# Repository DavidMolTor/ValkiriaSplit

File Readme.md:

# VALKIRIA SPLIT

Completely wireless, split mechanical keyboard based on the nRF52840 microcontroller, with independent wireless operation for each half.

## Introduction

This is a personal project born from my interest in exploring the world of ergonomic mechanical keyboards. After looking at several existing designs, I found that none of them offered exactly what I was looking for, so I decided to design and build my own.

I took a bit of a gamble by choosing a Corne-inspired layout without a dedicated number row, opting for a more minimal design. However, if I find that this layout does not suit my needs, I plan to develop a new version with additional keys.

## Features

 - Completely wireless operation of both sides.

 - Rechargeable and replaceable battery.

 - Hot-swappable chocolate sockets.

 - Full RGB with switchable regulator.

 - Two 1.08" MIP displays.

 - Rotary encoders with push button.

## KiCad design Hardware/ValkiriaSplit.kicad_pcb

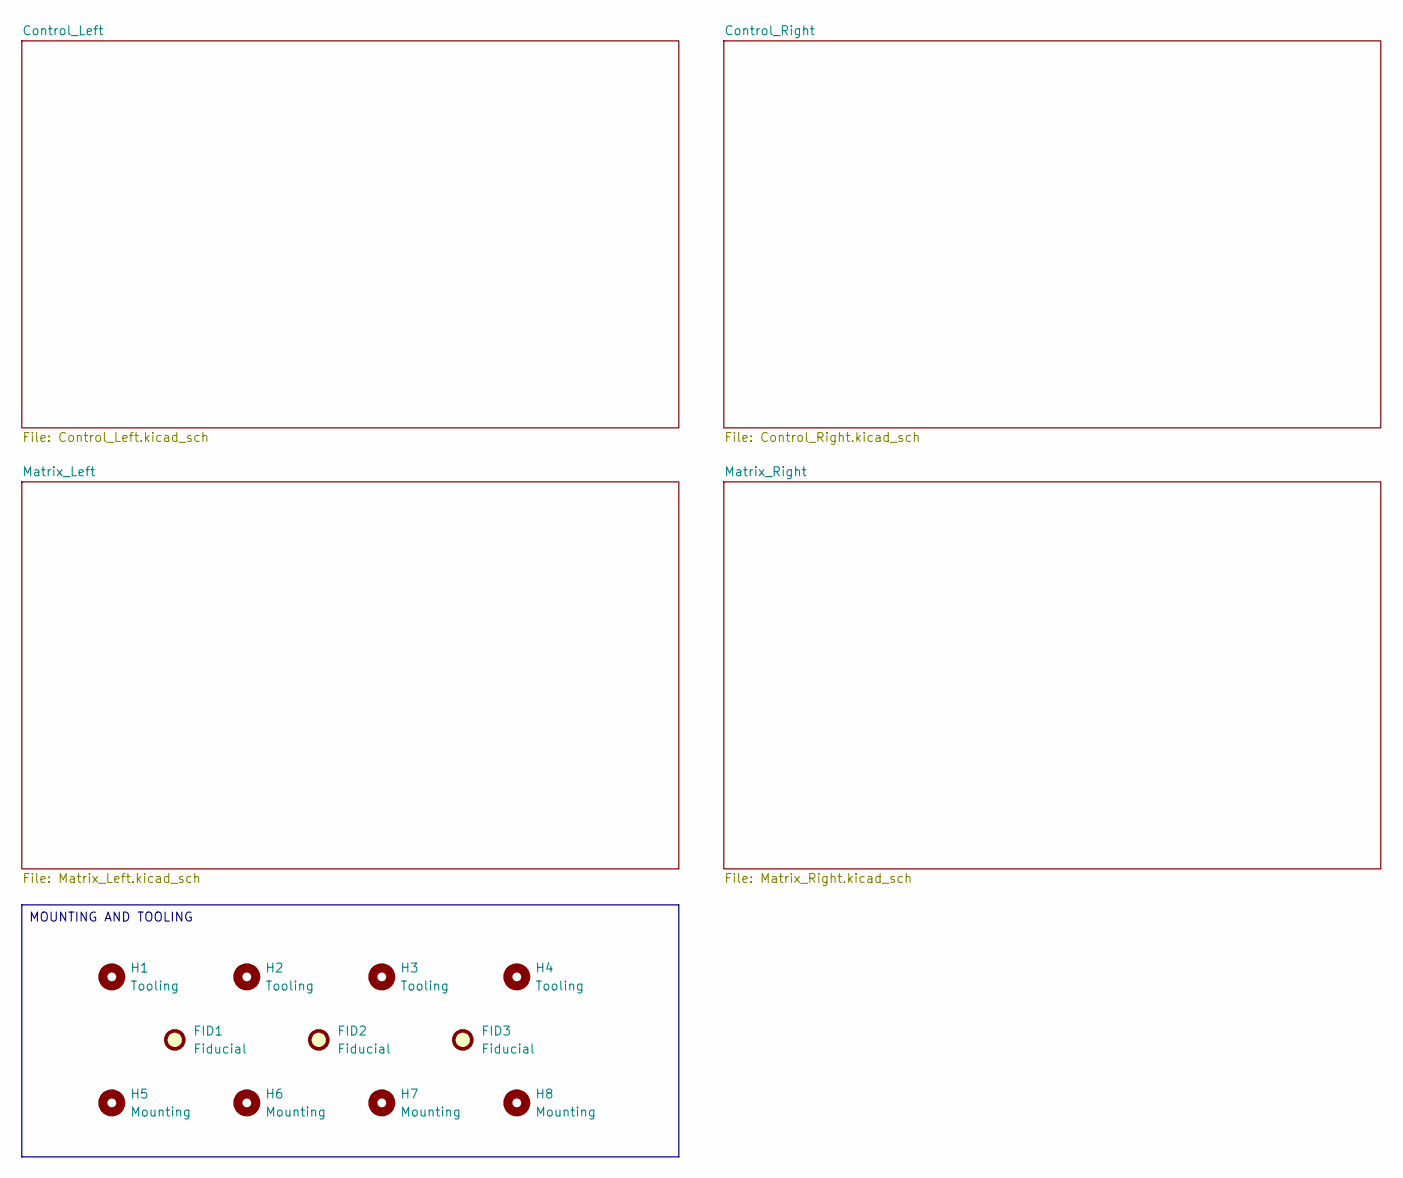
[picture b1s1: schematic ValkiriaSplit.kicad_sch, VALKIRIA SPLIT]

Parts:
FID1, FID2, FID3: Fiducial; Fiducial_1mm_Mask2mm
H1, H2, H3, H4: Tooling; ToolingHole_1.152mm
H5, H6, H7, H8: Mounting; MountingHole_2.2mm_M2

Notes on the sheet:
MOUNTING AND TOOLING

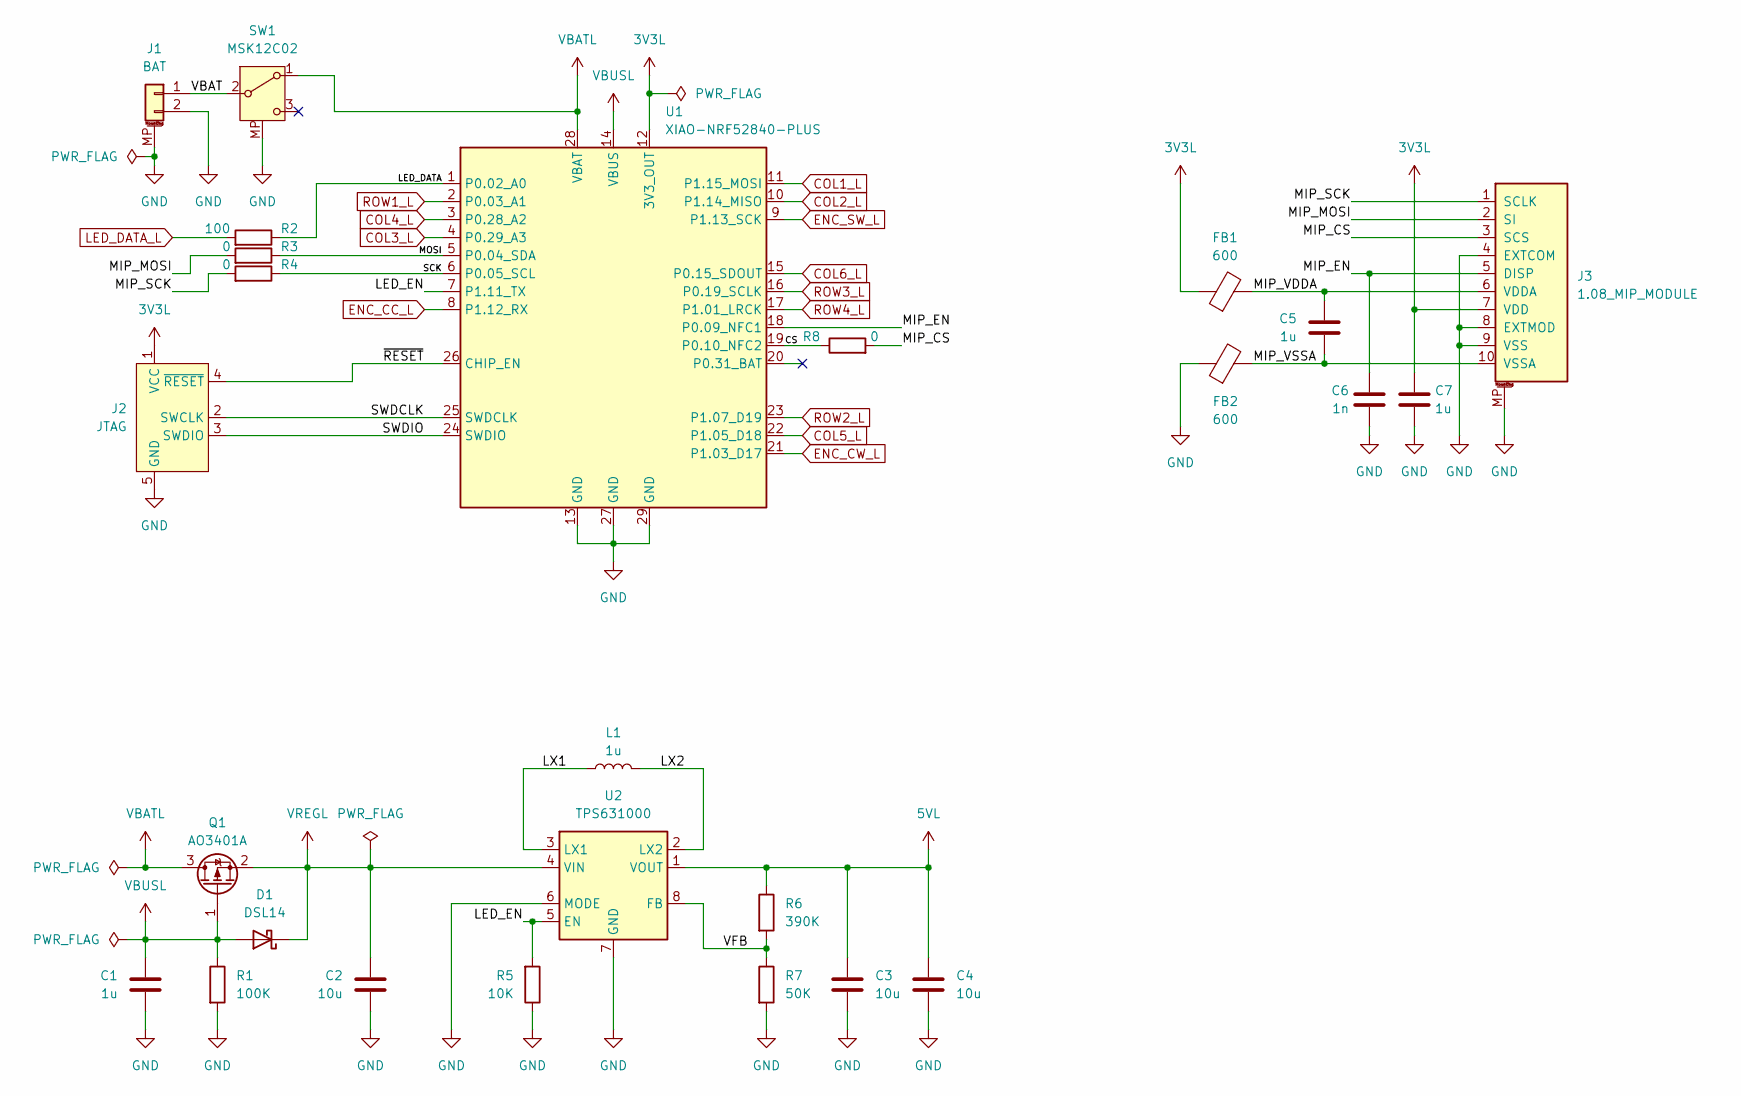
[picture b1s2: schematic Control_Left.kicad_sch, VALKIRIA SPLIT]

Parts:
C1, C5, C7: 1u; C_0603_1608Metric; Manufacturer Part CL10A105KB8NNNC; JLC Part C15849
C2, C3, C4: 10u; C_0603_1608Metric; Manufacturer Part CL10A106MA8NRNC; JLC Part C96446
C6: 1n; C_0603_1608Metric; Manufacturer Part CL10B102KB8NNNC; JLC Part C1588
D1: DSL14; D_SOD-123F; Manufacturer Part DSL14; JLC Part C22466349
FB1, FB2: 600; L_0603_1608Metric; Manufacturer Part GZ1608D601TF; JLC Part C1002
J1: BAT; JST_ZH_1x02_P1.50MM_SMD_HORIZONTAL; Manufacturer Part ZH1.5-2P-WT; JLC Part C722913
J2: JTAG; JTAG_SWD_1X05_1.27MM_COMBO
J3: 1.08_MIP_MODULE; 1.08_MIP_MODULE_TALL; Manufacturer Part AFC07-S10FCC-00; JLC Part C11050
L1: 1u; L_Changjiang_FNR252012S; Manufacturer Part PNR252012-1R0N; JLC Part C19634042
Q1: AO3401A; SOT-23; Manufacturer Part AO3401A; JLC Part C15127
R1: 100K; R_0603_1608Metric; Manufacturer Part 0603WAF1003T5E; JLC Part C25803
R2: 100; R_0603_1608Metric; Manufacturer Part 0603WAF1000T5E; JLC Part C22775
R3, R4, R8: 0; R_0603_1608Metric; Manufacturer Part 0603WAF0000T5E; JLC Part C21189
R5: 10K; R_0603_1608Metric; Manufacturer Part 0603WAF1002T5E; JLC Part C25804
R6: 390K; R_0603_1608Metric; Manufacturer Part 0603WAF3903T5E; JLC Part C23150
R7: 50K; R_0603_1608Metric; Manufacturer Part 0603WAF4992T5E; JLC Part C23184
SW1: MSK12C02; Manufacturer Part MSK12C02-HB; JLC Part C431541
U1: XIAO-NRF52840-PLUS; XIAO-NRF52840-PLUS-SMD-EDGE
U2: TPS631000; SOT-5X3; Manufacturer Part TPS631000DRLR; JLC Part C5219190

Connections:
3V3L: C7.1, FB1.1, J2.1 (VCC), J3.7 (VDD), U1.12 (3V3_OUT)
5VL: C3.1, C4.1, R6.1, U2.1 (VOUT); also elsewhere on the board
/Control_Left/CS: R8.1, U1.19 (P0.10_NFC2)
/Control_Left/LED_DATA: R2.1, U1.1 (P0.02_A0)
/Control_Left/LED_EN: R5.2, U1.7 (P1.11_TX), U2.5 (EN)
/Control_Left/LX1: L1.1, U2.3 (LX1)
/Control_Left/LX2: L1.2, U2.2 (LX2)
/Control_Left/MIP_CS: J3.3 (SCS), R8.2
/Control_Left/MIP_EN: C6.1, J3.5 (DISP), U1.18 (P0.09_NFC1)
/Control_Left/MIP_MOSI: J3.2 (SI), R3.2
/Control_Left/MIP_SCK: J3.1 (SCLK), R4.2
/Control_Left/MIP_VDDA: C5.1, FB1.2, J3.6 (VDDA)
/Control_Left/MIP_VSSA: C5.2, FB2.2, J3.10 (VSSA)
/Control_Left/MOSI: R3.1, U1.5 (P0.04_SDA)
/Control_Left/SCK: R4.1, U1.6 (P0.05_SCL)
/Control_Left/SWDCLK: J2.2 (SWCLK), U1.25 (SWDCLK)
/Control_Left/SWDIO: J2.3 (SWDIO), U1.24 (SWDIO)
/Control_Left/VBAT: J1.1, SW1.2 (B)
/Control_Left/VFB: R6.2, R7.1, U2.8 (FB)
/Control_Left/~RESET: J2.4 (~RESET), U1.26 (CHIP_EN)
COL1_L: U1.11 (P1.15_MOSI); also elsewhere on the board
COL2_L: U1.10 (P1.14_MISO); also elsewhere on the board
COL3_L: U1.4 (P0.29_A3); also elsewhere on the board
COL4_L: U1.3 (P0.28_A2); also elsewhere on the board
COL5_L: U1.22 (P1.05_D18); also elsewhere on the board
COL6_L: U1.15 (P0.15_SDOUT); also elsewhere on the board
ENC_CC_L: U1.8 (P1.12_RX); also elsewhere on the board
ENC_CW_L: U1.21 (P1.03_D17); also elsewhere on the board
ENC_SW_L: U1.9 (P1.13_SCK); also elsewhere on the board
GND: C1.2, C2.2, C3.2, C4.2, C6.2, C7.2, FB2.1, J1.2, J1.MP (MountPin), J2.5 (GND), J3.4 (EXTCOM), J3.8 (EXTMOD), J3.9 (VSS), J3.MP, R1.2, R5.1, R7.2, SW1.MP, U1.13 (GND), U1.27 (GND), U1.29 (GND), U2.6 (MODE), U2.7 (GND); also elsewhere on the board
LED_DATA_L: R2.2; also elsewhere on the board
ROW1_L: U1.2 (P0.03_A1); also elsewhere on the board
ROW2_L: U1.23 (P1.07_D19); also elsewhere on the board
ROW3_L: U1.16 (P0.19_SCLK); also elsewhere on the board
ROW4_L: U1.17 (P1.01_LRCK); also elsewhere on the board
VBATL: Q1.3 (D), SW1.1 (A), U1.28 (VBAT)
VBUSL: C1.1, D1.2 (A), Q1.1 (G), R1.1, U1.14 (VBUS)
VREGL: C2.1, D1.1 (K), Q1.2 (S), U2.4 (VIN)

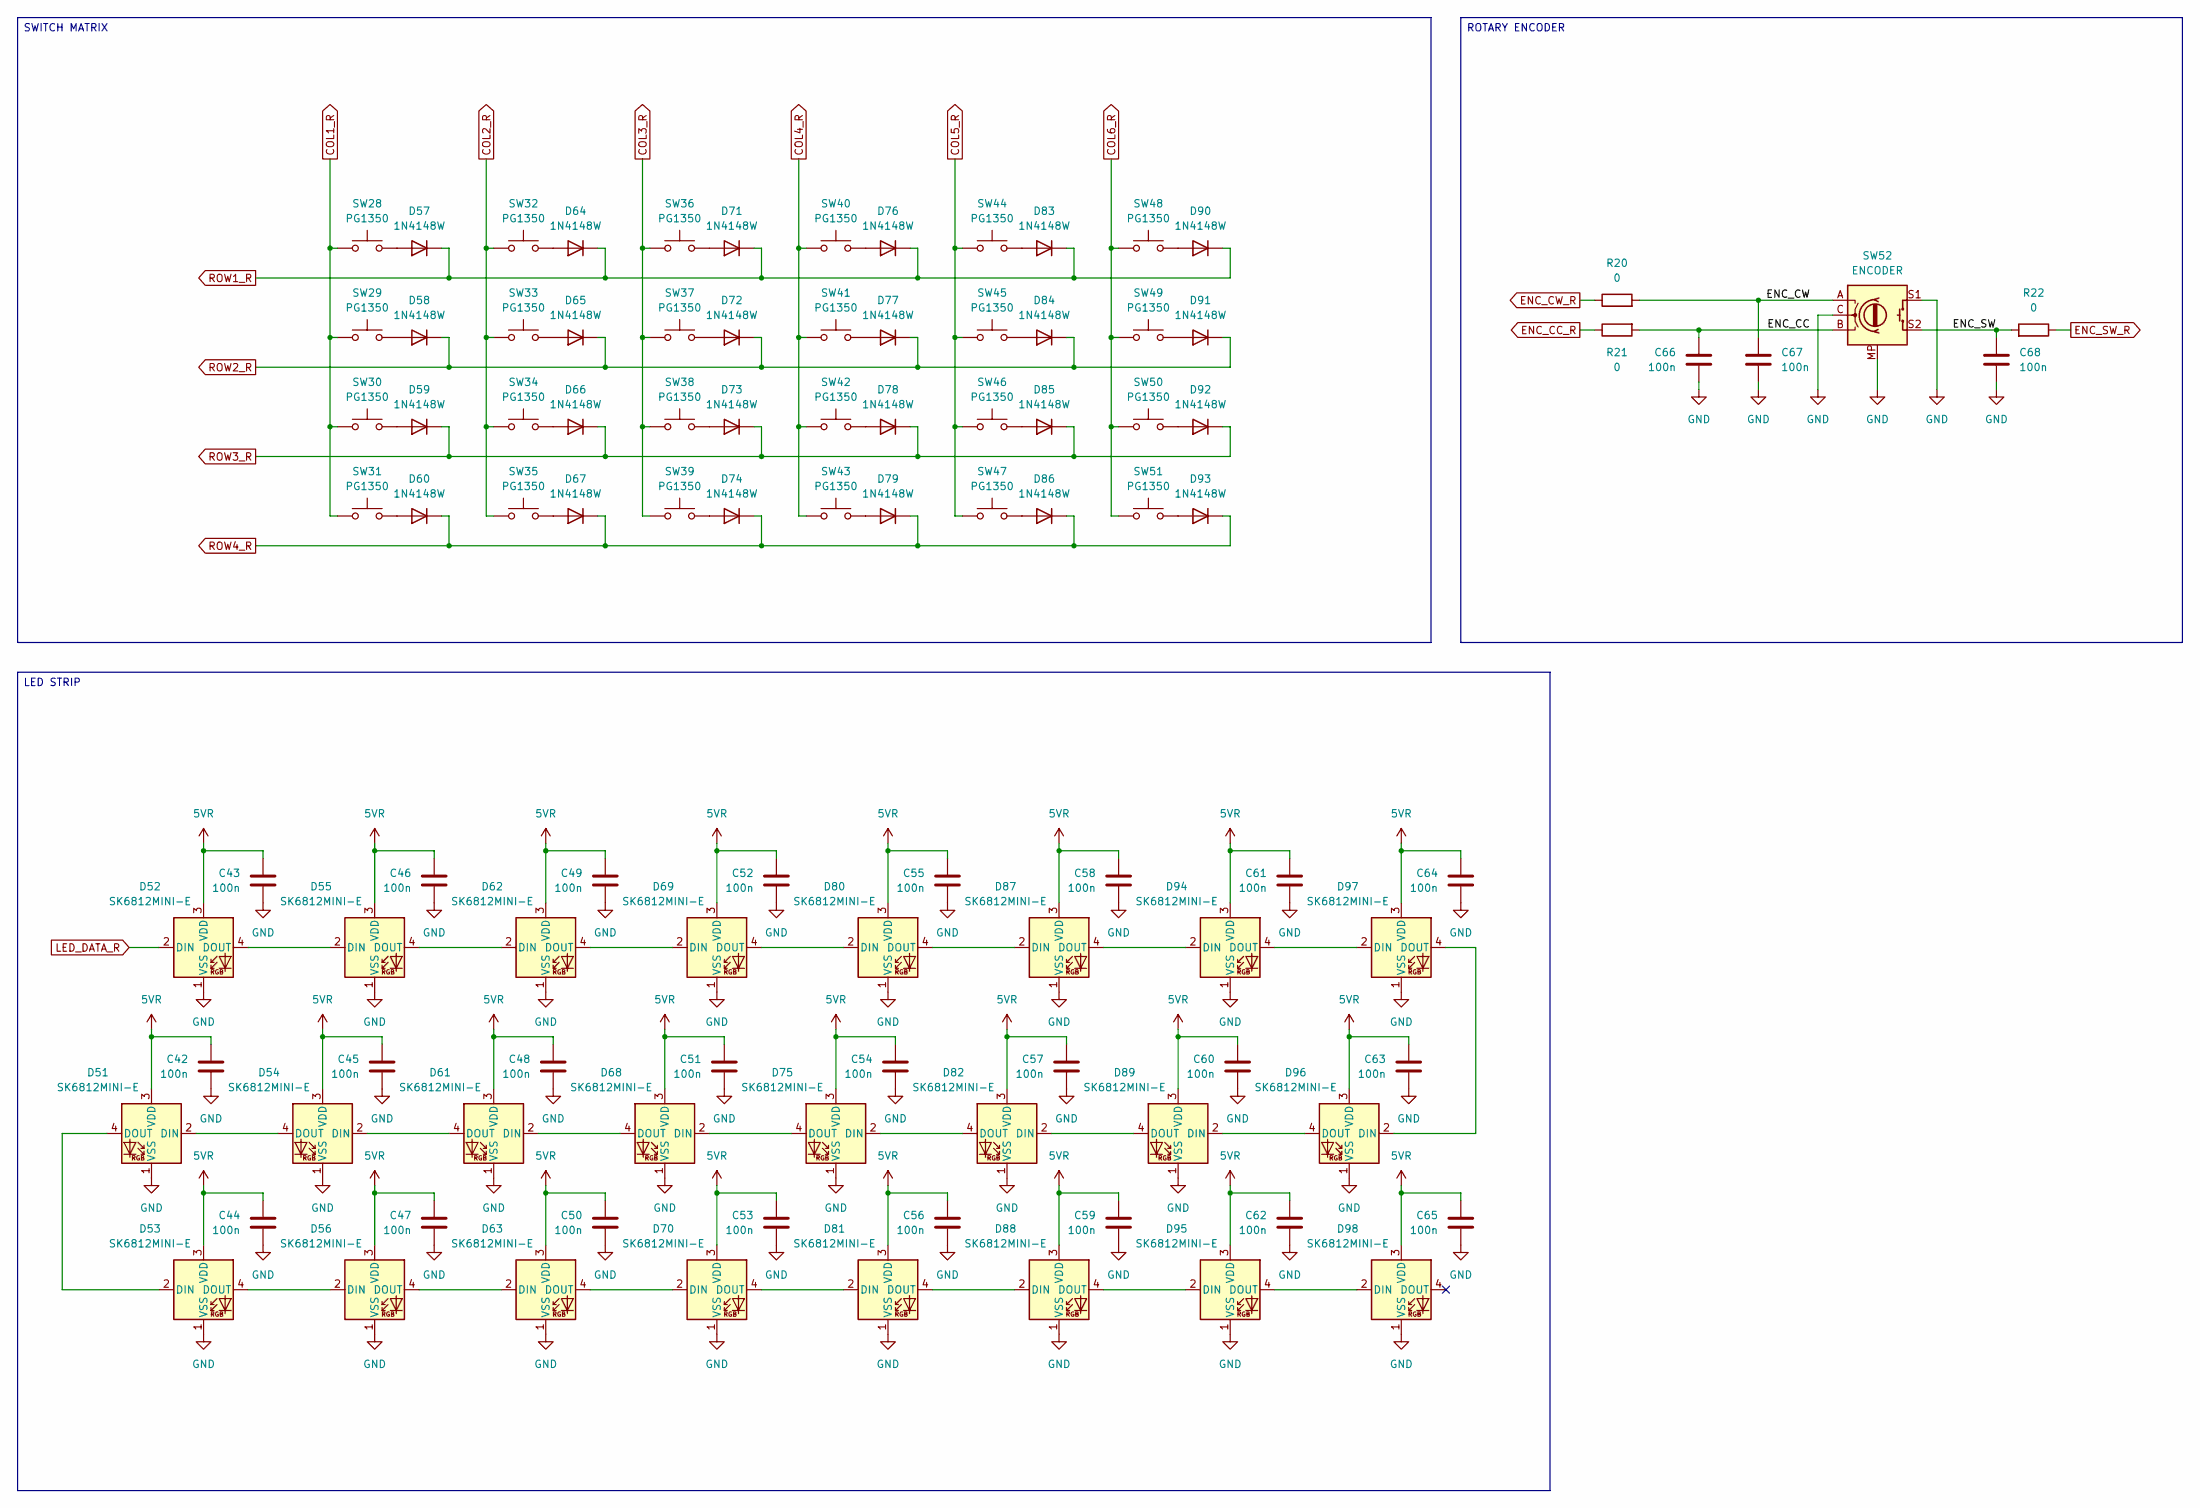
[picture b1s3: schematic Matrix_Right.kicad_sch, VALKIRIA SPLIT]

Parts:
C42, C43, C44, C45, C46, C47, C48, C49, C50, C51, C52, C53, C54, C55, C56, C57, C58, C59, C60, C61, C62, C63, C64, C65, C66, C67, C68: 100n; C_0603_1608Metric; Manufacturer Part CC0603KRX7R9BB104; JLC Part C14663
D51, D52, D53, D54, D55, D56, D61, D62, D63, D68, D69, D70, D75, D80, D81, D82, D87, D88, D89, D94, D95, D96, D97, D98: SK6812MINI-E; LED_SK6812MINI-E_3.2x2.8mm_P1.5mm_ReverseMount; Manufacturer Part GL6028RGB01H-T; JLC Part C51933369
D57, D58, D59, D60, D64, D65, D66, D67, D71, D72, D73, D74, D76, D77, D78, D79, D83, D84, D85, D86, D90, D91, D92, D93: 1N4148W; DIODE-SOD-123-FLAT; Manufacturer Part 1N4148W; JLC Part C81598
R20, R21, R22: 0; R_0603_1608Metric; Manufacturer Part 0603WAF0000T5E; JLC Part C21189
SW28, SW29, SW30, SW31, SW32, SW33, SW34, SW35, SW36, SW37, SW38, SW39, SW40, SW41, SW42, SW43, SW44, SW45, SW46, SW47, SW48, SW49, SW50, SW51: PG1350; PG1350_1.00u_PCB_TIGHT; Manufacturer Part CPG135001S30; JLC Part C5333465
SW52: ENCODER; ALPS_EC11J_ENCODER; Manufacturer Part EC11J1525402; JLC Part C209762

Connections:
5VR: C42.1, C43.1, C44.1, C45.1, C46.1, C47.1, C48.1, C49.1, C50.1, C51.1, C52.1, C53.1, C54.1, C55.1, C56.1, C57.1, C58.1, C59.1, C60.1, C61.1, C62.1, C63.1, C64.1, C65.1, D51.3 (VDD), D52.3 (VDD), D53.3 (VDD), D54.3 (VDD), D55.3 (VDD), D56.3 (VDD), D61.3 (VDD), D62.3 (VDD), D63.3 (VDD), D68.3 (VDD), D69.3 (VDD), D70.3 (VDD), D75.3 (VDD), D80.3 (VDD), D81.3 (VDD), D82.3 (VDD), D87.3 (VDD), D88.3 (VDD), D89.3 (VDD), D94.3 (VDD), D95.3 (VDD), D96.3 (VDD), D97.3 (VDD), D98.3 (VDD); also elsewhere on the board
/Matrix_Right/ENC_CC: C66.1, R21.2, SW52.B
/Matrix_Right/ENC_CW: C67.1, R20.2, SW52.A
/Matrix_Right/ENC_SW: C68.1, R22.2, SW52.S2
COL1_R: SW28.1, SW29.1, SW30.1, SW31.1; also elsewhere on the board
COL2_R: SW32.1, SW33.1, SW34.1, SW35.1; also elsewhere on the board
COL3_R: SW36.1, SW37.1, SW38.1, SW39.1; also elsewhere on the board
COL4_R: SW40.1, SW41.1, SW42.1, SW43.1; also elsewhere on the board
COL5_R: SW44.1, SW45.1, SW46.1, SW47.1; also elsewhere on the board
COL6_R: SW48.1, SW49.1, SW50.1, SW51.1; also elsewhere on the board
ENC_CC_R: R21.1; also elsewhere on the board
ENC_CW_R: R20.1; also elsewhere on the board
ENC_SW_R: R22.1; also elsewhere on the board
GND: C42.2, C43.2, C44.2, C45.2, C46.2, C47.2, C48.2, C49.2, C50.2, C51.2, C52.2, C53.2, C54.2, C55.2, C56.2, C57.2, C58.2, C59.2, C60.2, C61.2, C62.2, C63.2, C64.2, C65.2, C66.2, C67.2, C68.2, D51.1 (VSS), D52.1 (VSS), D53.1 (VSS), D54.1 (VSS), D55.1 (VSS), D56.1 (VSS), D61.1 (VSS), D62.1 (VSS), D63.1 (VSS), D68.1 (VSS), D69.1 (VSS), D70.1 (VSS), D75.1 (VSS), D80.1 (VSS), D81.1 (VSS), D82.1 (VSS), D87.1 (VSS), D88.1 (VSS), D89.1 (VSS), D94.1 (VSS), D95.1 (VSS), D96.1 (VSS), D97.1 (VSS), D98.1 (VSS), SW52.C, SW52.MP, SW52.S1; also elsewhere on the board
LED_DATA_R: D52.2 (DIN); also elsewhere on the board
unnamed: D51.2 (DIN), D54.4 (DOUT)
unnamed: D51.4 (DOUT), D53.2 (DIN)
unnamed: D52.4 (DOUT), D55.2 (DIN)
unnamed: D53.4 (DOUT), D56.2 (DIN)
unnamed: D54.2 (DIN), D61.4 (DOUT)
unnamed: D55.4 (DOUT), D62.2 (DIN)
unnamed: D56.4 (DOUT), D63.2 (DIN)
unnamed: D57.2 (A), SW28.2
unnamed: D58.2 (A), SW29.2
unnamed: D59.2 (A), SW30.2
unnamed: D60.2 (A), SW31.2
unnamed: D61.2 (DIN), D68.4 (DOUT)
unnamed: D62.4 (DOUT), D69.2 (DIN)
unnamed: D63.4 (DOUT), D70.2 (DIN)
unnamed: D64.2 (A), SW32.2
unnamed: D65.2 (A), SW33.2
unnamed: D66.2 (A), SW34.2
unnamed: D67.2 (A), SW35.2
unnamed: D68.2 (DIN), D75.4 (DOUT)
unnamed: D69.4 (DOUT), D80.2 (DIN)
unnamed: D70.4 (DOUT), D81.2 (DIN)
unnamed: D71.2 (A), SW36.2
unnamed: D72.2 (A), SW37.2
unnamed: D73.2 (A), SW38.2
unnamed: D74.2 (A), SW39.2
unnamed: D75.2 (DIN), D82.4 (DOUT)
unnamed: D76.2 (A), SW40.2
unnamed: D77.2 (A), SW41.2
unnamed: D78.2 (A), SW42.2
unnamed: D79.2 (A), SW43.2
unnamed: D80.4 (DOUT), D87.2 (DIN)
unnamed: D81.4 (DOUT), D88.2 (DIN)
unnamed: D82.2 (DIN), D89.4 (DOUT)
unnamed: D83.2 (A), SW44.2
unnamed: D84.2 (A), SW45.2
unnamed: D85.2 (A), SW46.2
unnamed: D86.2 (A), SW47.2
unnamed: D87.4 (DOUT), D94.2 (DIN)
unnamed: D88.4 (DOUT), D95.2 (DIN)
unnamed: D89.2 (DIN), D96.4 (DOUT)
unnamed: D90.2 (A), SW48.2
unnamed: D91.2 (A), SW49.2
unnamed: D92.2 (A), SW50.2
unnamed: D93.2 (A), SW51.2
unnamed: D94.4 (DOUT), D97.2 (DIN)
unnamed: D95.4 (DOUT), D98.2 (DIN)
unnamed: D96.2 (DIN), D97.4 (DOUT)
ROW1_R: D57.1 (K), D64.1 (K), D71.1 (K), D76.1 (K), D83.1 (K), D90.1 (K); also elsewhere on the board
ROW2_R: D58.1 (K), D65.1 (K), D72.1 (K), D77.1 (K), D84.1 (K), D91.1 (K); also elsewhere on the board
ROW3_R: D59.1 (K), D66.1 (K), D73.1 (K), D78.1 (K), D85.1 (K), D92.1 (K); also elsewhere on the board
ROW4_R: D60.1 (K), D67.1 (K), D74.1 (K), D79.1 (K), D86.1 (K), D93.1 (K); also elsewhere on the board

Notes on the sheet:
SWITCH MATRIX
ROTARY ENCODER
LED STRIP

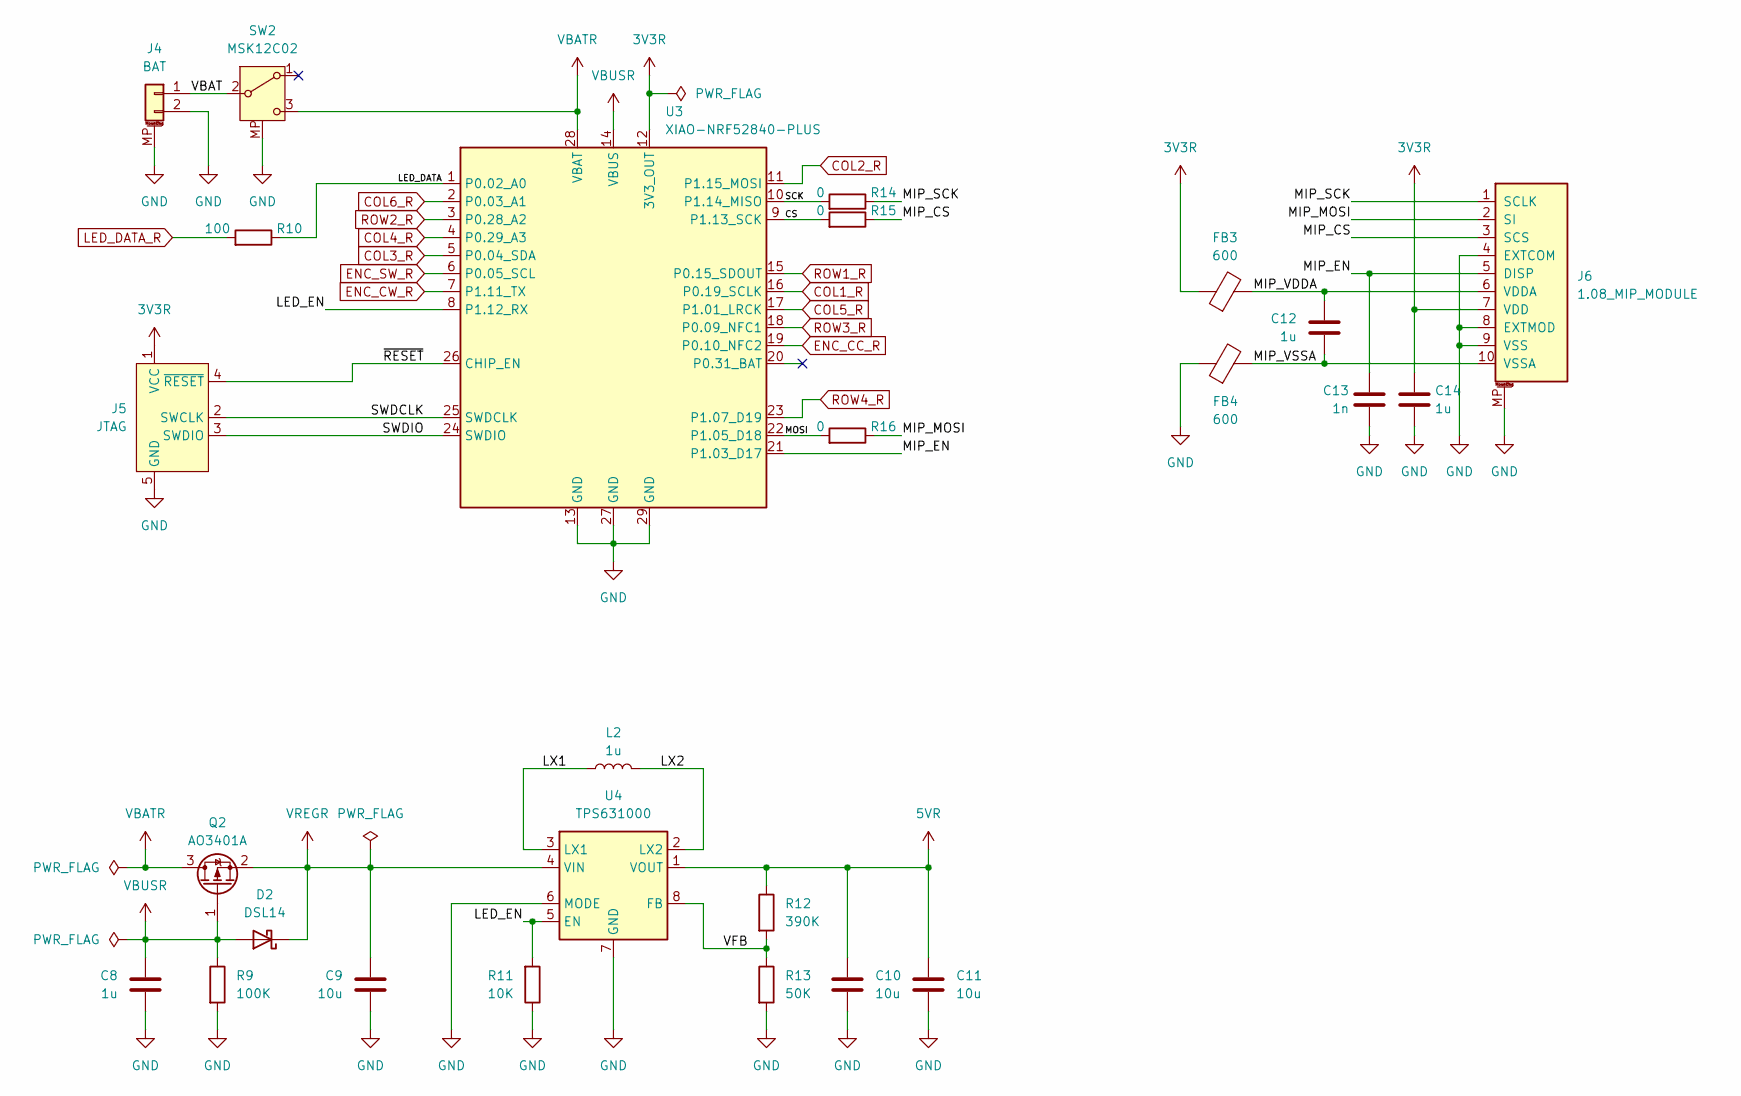
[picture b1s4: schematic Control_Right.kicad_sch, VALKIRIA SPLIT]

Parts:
C8, C12, C14: 1u; C_0603_1608Metric; Manufacturer Part CL10A105KB8NNNC; JLC Part C15849
C9, C10, C11: 10u; C_0603_1608Metric; Manufacturer Part CL10A106MA8NRNC; JLC Part C96446
C13: 1n; C_0603_1608Metric; Manufacturer Part CL10B102KB8NNNC; JLC Part C1588
D2: DSL14; D_SOD-123F; Manufacturer Part DSL14; JLC Part C22466349
FB3, FB4: 600; L_0603_1608Metric; Manufacturer Part GZ1608D601TF; JLC Part C1002
J4: BAT; JST_ZH_1x02_P1.50MM_SMD_HORIZONTAL; Manufacturer Part ZH1.5-2P-WT; JLC Part C722913
J5: JTAG; JTAG_SWD_1X05_1.27MM_COMBO
J6: 1.08_MIP_MODULE; 1.08_MIP_MODULE_TALL; Manufacturer Part AFC07-S10FCC-00; JLC Part C11050
L2: 1u; L_Changjiang_FNR252012S; Manufacturer Part PNR252012-1R0N; JLC Part C19634042
Q2: AO3401A; SOT-23; Manufacturer Part AO3401A; JLC Part C15127
R9: 100K; R_0603_1608Metric; Manufacturer Part 0603WAF1003T5E; JLC Part C25803
R10: 100; R_0603_1608Metric; Manufacturer Part 0603WAF1000T5E; JLC Part C22775
R11: 10K; R_0603_1608Metric; Manufacturer Part 0603WAF1002T5E; JLC Part C25804
R12: 390K; R_0603_1608Metric; Manufacturer Part 0603WAF3903T5E; JLC Part C23150
R13: 50K; R_0603_1608Metric; Manufacturer Part 0603WAF4992T5E; JLC Part C23184
R14, R15, R16: 0; R_0603_1608Metric; Manufacturer Part 0603WAF0000T5E; JLC Part C21189
SW2: MSK12C02; Manufacturer Part MSK12C02-HB; JLC Part C431541
U3: XIAO-NRF52840-PLUS; XIAO-NRF52840-PLUS-SMD-EDGE
U4: TPS631000; SOT-5X3; Manufacturer Part TPS631000DRLR; JLC Part C5219190

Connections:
3V3R: C14.1, FB3.1, J5.1 (VCC), J6.7 (VDD), U3.12 (3V3_OUT)
5VR: C10.1, C11.1, R12.1, U4.1 (VOUT); also elsewhere on the board
/Control_Right/CS: R15.2, U3.9 (P1.13_SCK)
/Control_Right/LED_DATA: R10.1, U3.1 (P0.02_A0)
/Control_Right/LED_EN: R11.2, U3.8 (P1.12_RX), U4.5 (EN)
/Control_Right/LX1: L2.1, U4.3 (LX1)
/Control_Right/LX2: L2.2, U4.2 (LX2)
/Control_Right/MIP_CS: J6.3 (SCS), R15.1
/Control_Right/MIP_EN: C13.1, J6.5 (DISP), U3.21 (P1.03_D17)
/Control_Right/MIP_MOSI: J6.2 (SI), R16.1
/Control_Right/MIP_SCK: J6.1 (SCLK), R14.1
/Control_Right/MIP_VDDA: C12.1, FB3.2, J6.6 (VDDA)
/Control_Right/MIP_VSSA: C12.2, FB4.2, J6.10 (VSSA)
/Control_Right/MOSI: R16.2, U3.22 (P1.05_D18)
/Control_Right/SCK: R14.2, U3.10 (P1.14_MISO)
/Control_Right/SWDCLK: J5.2 (SWCLK), U3.25 (SWDCLK)
/Control_Right/SWDIO: J5.3 (SWDIO), U3.24 (SWDIO)
/Control_Right/VBAT: J4.1, SW2.2 (B)
/Control_Right/VFB: R12.2, R13.1, U4.8 (FB)
/Control_Right/~RESET: J5.4 (~RESET), U3.26 (CHIP_EN)
COL1_R: U3.16 (P0.19_SCLK); also elsewhere on the board
COL2_R: U3.11 (P1.15_MOSI); also elsewhere on the board
COL3_R: U3.5 (P0.04_SDA); also elsewhere on the board
COL4_R: U3.4 (P0.29_A3); also elsewhere on the board
COL5_R: U3.17 (P1.01_LRCK); also elsewhere on the board
COL6_R: U3.2 (P0.03_A1); also elsewhere on the board
ENC_CC_R: U3.19 (P0.10_NFC2); also elsewhere on the board
ENC_CW_R: U3.7 (P1.11_TX); also elsewhere on the board
ENC_SW_R: U3.6 (P0.05_SCL); also elsewhere on the board
GND: C8.2, C9.2, C10.2, C11.2, C13.2, C14.2, FB4.1, J4.2, J4.MP (MountPin), J5.5 (GND), J6.4 (EXTCOM), J6.8 (EXTMOD), J6.9 (VSS), J6.MP, R9.2, R11.1, R13.2, SW2.MP, U3.13 (GND), U3.27 (GND), U3.29 (GND), U4.6 (MODE), U4.7 (GND); also elsewhere on the board
LED_DATA_R: R10.2; also elsewhere on the board
ROW1_R: U3.15 (P0.15_SDOUT); also elsewhere on the board
ROW2_R: U3.3 (P0.28_A2); also elsewhere on the board
ROW3_R: U3.18 (P0.09_NFC1); also elsewhere on the board
ROW4_R: U3.23 (P1.07_D19); also elsewhere on the board
VBATR: Q2.3 (D), SW2.3 (C), U3.28 (VBAT)
VBUSR: C8.1, D2.2 (A), Q2.1 (G), R9.1, U3.14 (VBUS)
VREGR: C9.1, D2.1 (K), Q2.2 (S), U4.4 (VIN)

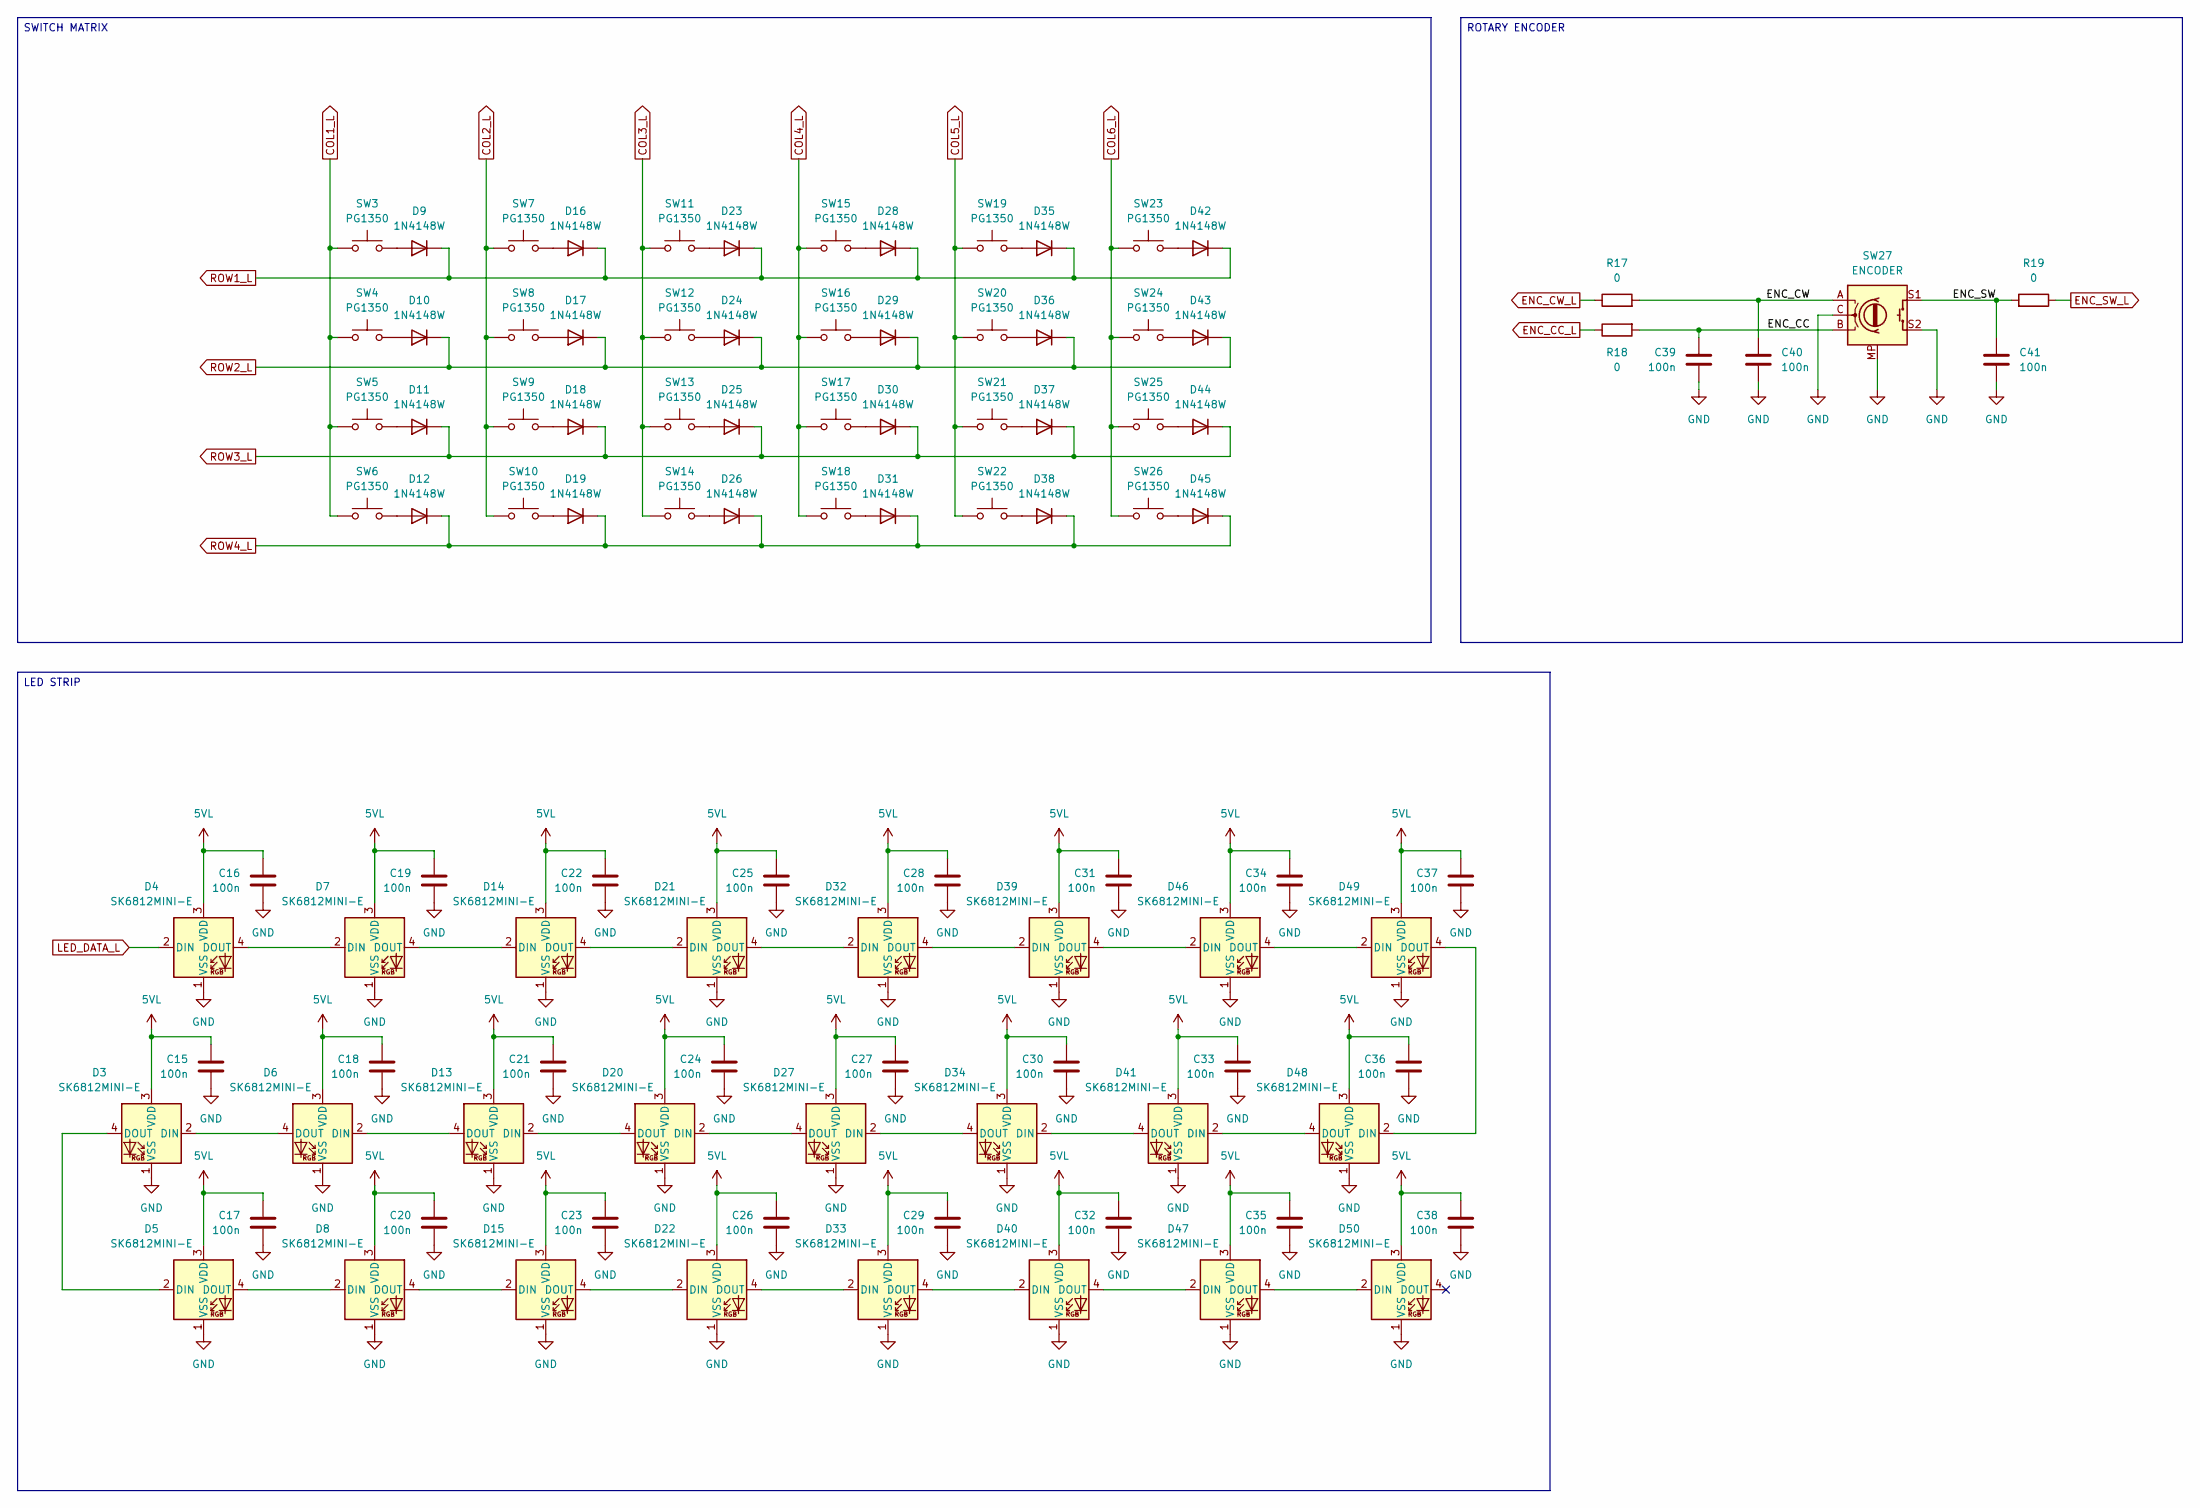
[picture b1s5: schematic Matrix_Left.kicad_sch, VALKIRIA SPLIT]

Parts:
C15, C16, C17, C18, C19, C20, C21, C22, C23, C24, C25, C26, C27, C28, C29, C30, C31, C32, C33, C34, C35, C36, C37, C38, C39, C40, C41: 100n; C_0603_1608Metric; Manufacturer Part CC0603KRX7R9BB104; JLC Part C14663
D3, D4, D5, D6, D7, D8, D13, D14, D15, D20, D21, D22, D27, D32, D33, D34, D39, D40, D41, D46, D47, D48, D49, D50: SK6812MINI-E; LED_SK6812MINI-E_3.2x2.8mm_P1.5mm_ReverseMount; Manufacturer Part GL6028RGB01H-T; JLC Part C51933369
D9, D10, D11, D12, D16, D17, D18, D19, D23, D24, D25, D26, D28, D29, D30, D31, D35, D36, D37, D38, D42, D43, D44, D45: 1N4148W; DIODE-SOD-123-FLAT; Manufacturer Part 1N4148W; JLC Part C81598
R17, R18, R19: 0; R_0603_1608Metric; Manufacturer Part 0603WAF0000T5E; JLC Part C21189
SW3, SW4, SW5, SW6, SW7, SW8, SW9, SW10, SW11, SW12, SW13, SW14, SW15, SW16, SW17, SW18, SW19, SW20, SW21, SW22, SW23, SW24, SW25, SW26: PG1350; PG1350_1.00u_PCB_TIGHT; Manufacturer Part CPG135001S30; JLC Part C5333465
SW27: ENCODER; ALPS_EC11J_ENCODER; Manufacturer Part EC11J1525402; JLC Part C209762

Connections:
5VL: C15.1, C16.1, C17.1, C18.1, C19.1, C20.1, C21.1, C22.1, C23.1, C24.1, C25.1, C26.1, C27.1, C28.1, C29.1, C30.1, C31.1, C32.1, C33.1, C34.1, C35.1, C36.1, C37.1, C38.1, D3.3 (VDD), D4.3 (VDD), D5.3 (VDD), D6.3 (VDD), D7.3 (VDD), D8.3 (VDD), D13.3 (VDD), D14.3 (VDD), D15.3 (VDD), D20.3 (VDD), D21.3 (VDD), D22.3 (VDD), D27.3 (VDD), D32.3 (VDD), D33.3 (VDD), D34.3 (VDD), D39.3 (VDD), D40.3 (VDD), D41.3 (VDD), D46.3 (VDD), D47.3 (VDD), D48.3 (VDD), D49.3 (VDD), D50.3 (VDD); also elsewhere on the board
/Matrix_Left/ENC_CC: C39.1, R18.2, SW27.B
/Matrix_Left/ENC_CW: C40.1, R17.2, SW27.A
/Matrix_Left/ENC_SW: C41.1, R19.2, SW27.S1
COL1_L: SW3.1, SW4.1, SW5.1, SW6.1; also elsewhere on the board
COL2_L: SW7.1, SW8.1, SW9.1, SW10.1; also elsewhere on the board
COL3_L: SW11.1, SW12.1, SW13.1, SW14.1; also elsewhere on the board
COL4_L: SW15.1, SW16.1, SW17.1, SW18.1; also elsewhere on the board
COL5_L: SW19.1, SW20.1, SW21.1, SW22.1; also elsewhere on the board
COL6_L: SW23.1, SW24.1, SW25.1, SW26.1; also elsewhere on the board
ENC_CC_L: R18.1; also elsewhere on the board
ENC_CW_L: R17.1; also elsewhere on the board
ENC_SW_L: R19.1; also elsewhere on the board
GND: C15.2, C16.2, C17.2, C18.2, C19.2, C20.2, C21.2, C22.2, C23.2, C24.2, C25.2, C26.2, C27.2, C28.2, C29.2, C30.2, C31.2, C32.2, C33.2, C34.2, C35.2, C36.2, C37.2, C38.2, C39.2, C40.2, C41.2, D3.1 (VSS), D4.1 (VSS), D5.1 (VSS), D6.1 (VSS), D7.1 (VSS), D8.1 (VSS), D13.1 (VSS), D14.1 (VSS), D15.1 (VSS), D20.1 (VSS), D21.1 (VSS), D22.1 (VSS), D27.1 (VSS), D32.1 (VSS), D33.1 (VSS), D34.1 (VSS), D39.1 (VSS), D40.1 (VSS), D41.1 (VSS), D46.1 (VSS), D47.1 (VSS), D48.1 (VSS), D49.1 (VSS), D50.1 (VSS), SW27.C, SW27.MP, SW27.S2; also elsewhere on the board
LED_DATA_L: D4.2 (DIN); also elsewhere on the board
unnamed: D3.2 (DIN), D6.4 (DOUT)
unnamed: D3.4 (DOUT), D5.2 (DIN)
unnamed: D4.4 (DOUT), D7.2 (DIN)
unnamed: D5.4 (DOUT), D8.2 (DIN)
unnamed: D9.2 (A), SW3.2
unnamed: D10.2 (A), SW4.2
unnamed: D11.2 (A), SW5.2
unnamed: D12.2 (A), SW6.2
unnamed: D13.2 (DIN), D20.4 (DOUT)
unnamed: D6.2 (DIN), D13.4 (DOUT)
unnamed: D7.4 (DOUT), D14.2 (DIN)
unnamed: D14.4 (DOUT), D21.2 (DIN)
unnamed: D8.4 (DOUT), D15.2 (DIN)
unnamed: D15.4 (DOUT), D22.2 (DIN)
unnamed: D16.2 (A), SW7.2
unnamed: D17.2 (A), SW8.2
unnamed: D18.2 (A), SW9.2
unnamed: D19.2 (A), SW10.2
unnamed: D20.2 (DIN), D27.4 (DOUT)
unnamed: D21.4 (DOUT), D32.2 (DIN)
unnamed: D22.4 (DOUT), D33.2 (DIN)
unnamed: D23.2 (A), SW11.2
unnamed: D24.2 (A), SW12.2
unnamed: D25.2 (A), SW13.2
unnamed: D26.2 (A), SW14.2
unnamed: D27.2 (DIN), D34.4 (DOUT)
unnamed: D28.2 (A), SW15.2
unnamed: D29.2 (A), SW16.2
unnamed: D30.2 (A), SW17.2
unnamed: D31.2 (A), SW18.2
unnamed: D32.4 (DOUT), D39.2 (DIN)
unnamed: D33.4 (DOUT), D40.2 (DIN)
unnamed: D34.2 (DIN), D41.4 (DOUT)
unnamed: D35.2 (A), SW19.2
unnamed: D36.2 (A), SW20.2
unnamed: D37.2 (A), SW21.2
unnamed: D38.2 (A), SW22.2
unnamed: D39.4 (DOUT), D46.2 (DIN)
unnamed: D40.4 (DOUT), D47.2 (DIN)
unnamed: D41.2 (DIN), D48.4 (DOUT)
unnamed: D42.2 (A), SW23.2
unnamed: D43.2 (A), SW24.2
unnamed: D44.2 (A), SW25.2
unnamed: D45.2 (A), SW26.2
unnamed: D46.4 (DOUT), D49.2 (DIN)
unnamed: D47.4 (DOUT), D50.2 (DIN)
unnamed: D48.2 (DIN), D49.4 (DOUT)
ROW1_L: D9.1 (K), D16.1 (K), D23.1 (K), D28.1 (K), D35.1 (K), D42.1 (K); also elsewhere on the board
ROW2_L: D10.1 (K), D17.1 (K), D24.1 (K), D29.1 (K), D36.1 (K), D43.1 (K); also elsewhere on the board
ROW3_L: D11.1 (K), D18.1 (K), D25.1 (K), D30.1 (K), D37.1 (K), D44.1 (K); also elsewhere on the board
ROW4_L: D12.1 (K), D19.1 (K), D26.1 (K), D31.1 (K), D38.1 (K), D45.1 (K); also elsewhere on the board

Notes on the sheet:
LED STRIP
ROTARY ENCODER
SWITCH MATRIX
